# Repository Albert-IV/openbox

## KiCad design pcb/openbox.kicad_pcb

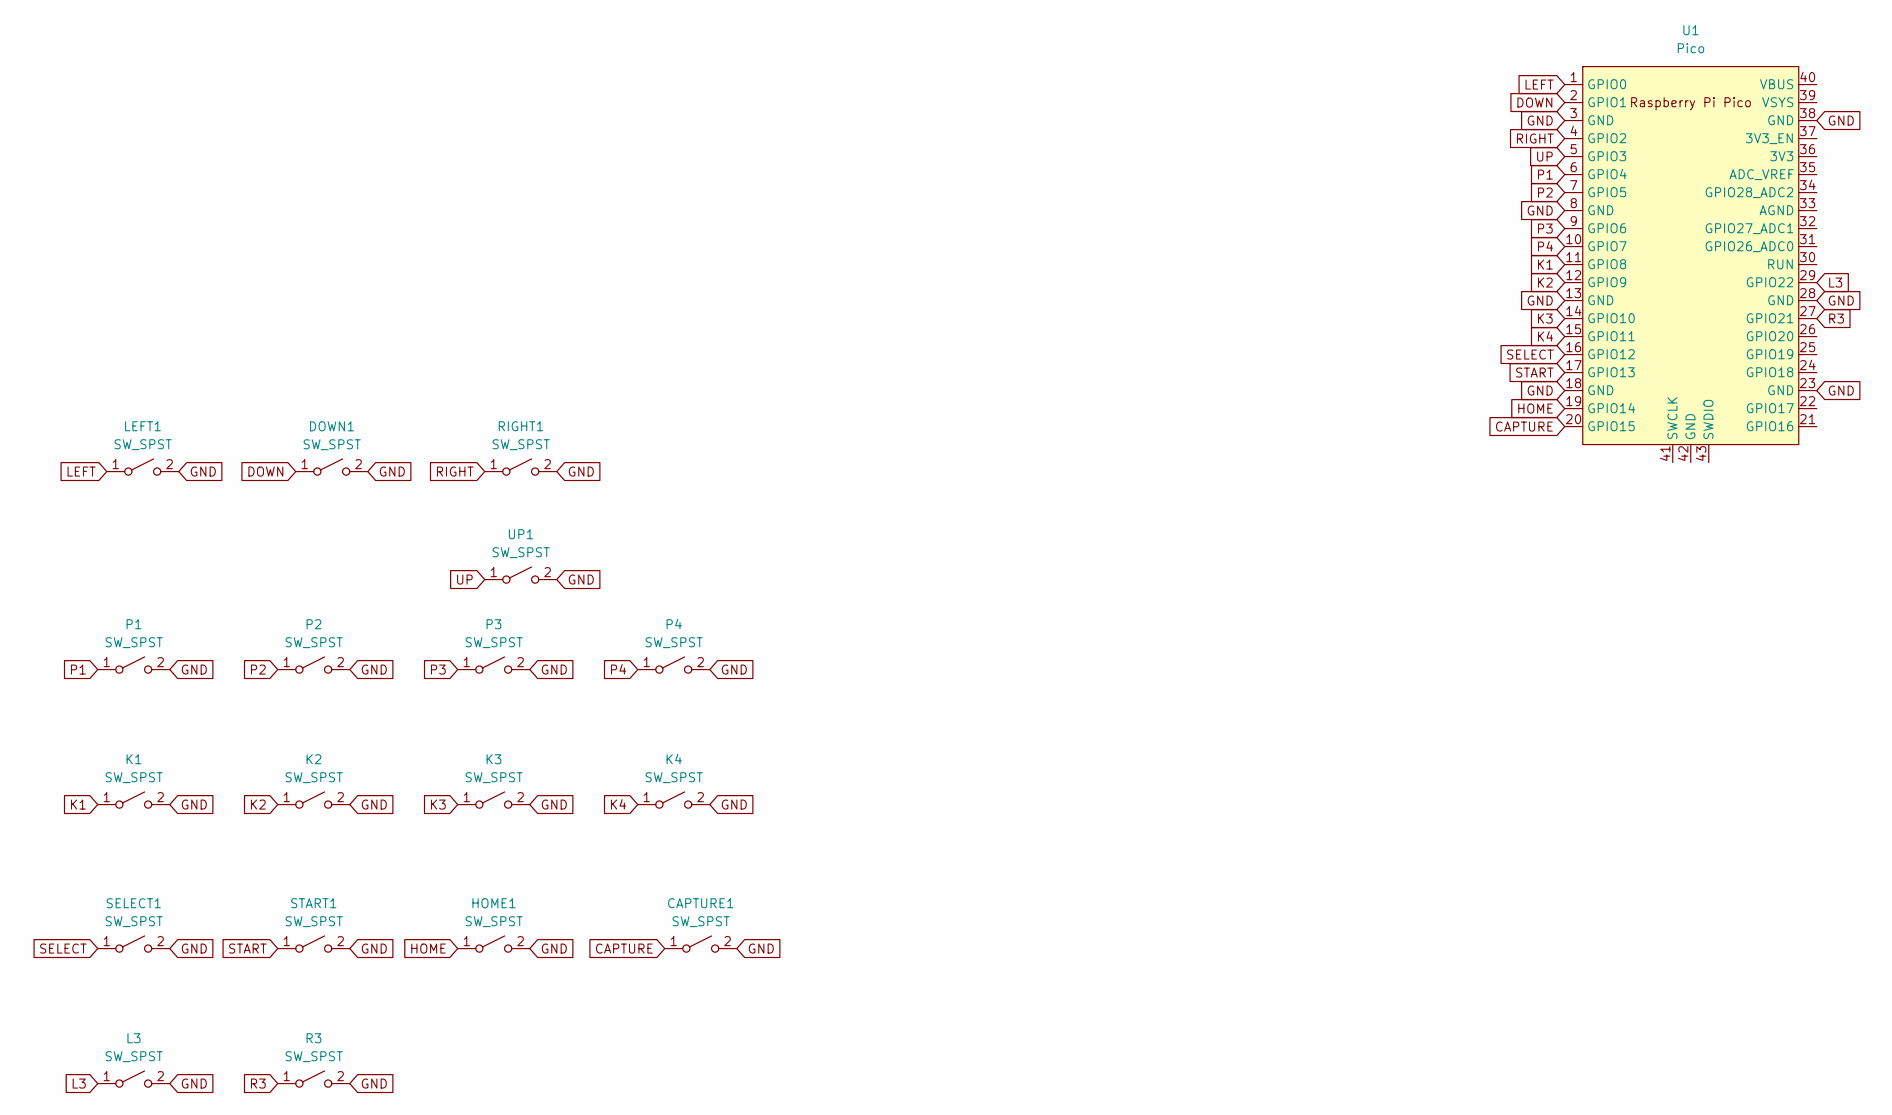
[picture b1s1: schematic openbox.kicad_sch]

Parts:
CAPTURE1: SW_SPST; SW_PUSH_6mm
DOWN1: SW_SPST; Kailh_socket_PG1350
HOME1: SW_SPST; SW_PUSH_6mm
K1, K2, K3, K4: SW_SPST; Kailh_socket_PG1350
L3: SW_SPST; SW_PUSH_6mm
LEFT1: SW_SPST; Kailh_socket_PG1350
P1, P2, P3, P4: SW_SPST; Kailh_socket_PG1350
R3: SW_SPST; SW_PUSH_6mm
RIGHT1: SW_SPST; Kailh_socket_PG1350
SELECT1: SW_SPST; SW_PUSH_6mm
START1: SW_SPST; SW_PUSH_6mm
U1: Pico; RPi_Pico_SMD_TH
UP1: SW_SPST; Kailh_socket_PG1350

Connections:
CAPTURE: CAPTURE1.1 (A), U1.20 (GPIO15)
DOWN: DOWN1.1 (A), U1.2 (GPIO1)
GND: CAPTURE1.2 (B), DOWN1.2 (B), HOME1.2 (B), K1.2 (B), K2.2 (B), K3.2 (B), K4.2 (B), L3.2 (B), LEFT1.2 (B), P1.2 (B), P2.2 (B), P3.2 (B), P4.2 (B), R3.2 (B), RIGHT1.2 (B), SELECT1.2 (B), START1.2 (B), U1.3 (GND), U1.8 (GND), U1.13 (GND), U1.18 (GND), U1.23 (GND), U1.28 (GND), U1.38 (GND), UP1.2 (B)
HOME: HOME1.1 (A), U1.19 (GPIO14)
K1: K1.1 (A), U1.11 (GPIO8)
K2: K2.1 (A), U1.12 (GPIO9)
K3: K3.1 (A), U1.14 (GPIO10)
K4: K4.1 (A), U1.15 (GPIO11)
L3: L3.1 (A), U1.29 (GPIO22)
LEFT: LEFT1.1 (A), U1.1 (GPIO0)
P1: P1.1 (A), U1.6 (GPIO4)
P2: P2.1 (A), U1.7 (GPIO5)
P3: P3.1 (A), U1.9 (GPIO6)
P4: P4.1 (A), U1.10 (GPIO7)
R3: R3.1 (A), U1.27 (GPIO21)
RIGHT: RIGHT1.1 (A), U1.4 (GPIO2)
SELECT: SELECT1.1 (A), U1.16 (GPIO12)
START: START1.1 (A), U1.17 (GPIO13)
UP: U1.5 (GPIO3), UP1.1 (A)

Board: 2 copper layers, 19 parts (0 on the bottom side), 19 nets, no tracks yet.

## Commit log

2022-10-08 Placeholder commit
2022-10-08 Pi placed, just have to place buttons
2022-10-19 Change extra buttons to 6x6mm push buttons
